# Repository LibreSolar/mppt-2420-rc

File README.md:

# MPPT charge controller for DIN rail mounting

 First prototype tested, but issues should still be expected.

Schematic: [PDF file](https://github.com/LibreSolar/mppt-2420-rc/raw/master/build/mppt-2420-rc_schematic.pdf)

Bill of Materials: [CSV file](build/mppt-2420-rc_bom.csv) or [interactive HTML BOM](https://libre.solar/mppt-2420-rc/build/mppt-2420-rc_ibom.html)

## Concept description

This charge controller is mainly developed to test the following features:

- Very compact and modular housing design for DIN rail mounting
- Thermal performance and maximum heat dissipation via internal heat sinks
- Performance of the internal OpAmp of the STM32G431 MCU for current measurement
- Dump-load control for small wind turbines using the existing PV reverse blocking MOSFET

## Features

- Solar/Wind input terminal
    - Max. 80V (100V MOSFETs used)
    - DC/DC converter inductor current max. 20A
- Battery output terminal
    - 10 V - 32 V (supporting 12 V and 24 V battery systems)
    - Max. current: 20A (limited by inductor current)
- New STM32G431 ARM MCU with advanced digital power conversion features
- Expandable via Olimex Universal Extension Connector (UEXT)
- Only single LED as power indicator. Additional user interface can be included in separate PCB in front panel housing and connected via UEXT
- CAN interface via RJ45 connectors
- Optional external temperature sensor (10k NTC)
- DIN rail mounting using Phoenix Contact BC series housing

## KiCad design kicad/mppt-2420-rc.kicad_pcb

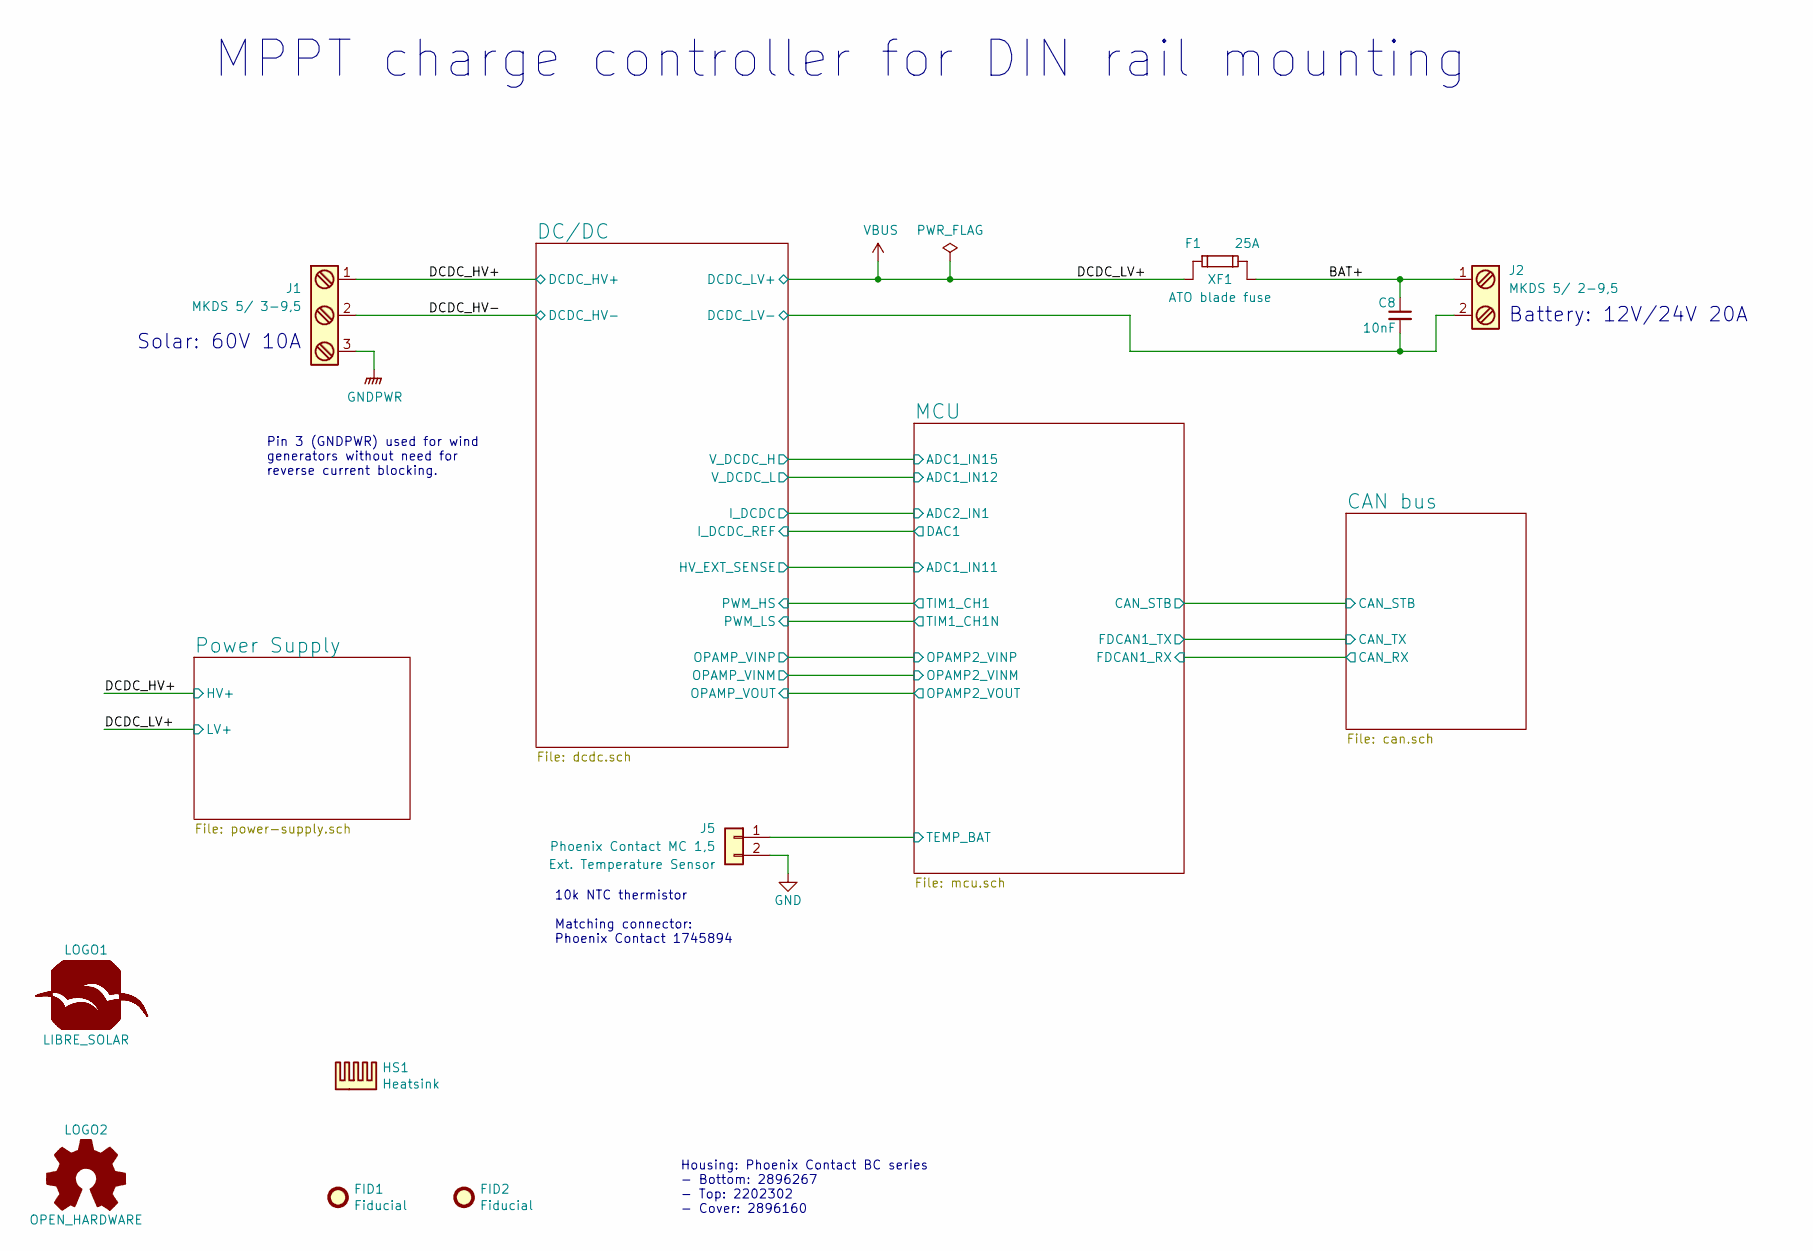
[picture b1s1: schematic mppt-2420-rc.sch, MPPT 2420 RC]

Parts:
C8: 10nF; C_0603_1608; PartNumber GCM188R72A103KA37D
F1: 25A; NULL; PartNumber 0287025.PXCN
FID1, FID2: Fiducial; Fiducial_0.7mm
HS1: Heatsink; Fischer_Elektronik_SK573_37,5; PartNumber SK573-37,5
J1: MKDS 5/ 3-9,5; Phoenix_Contact_MKDS_5-3-9,5; PartNumber 1714984
J2: MKDS 5/ 2-9,5; Phoenix_Contact_MKDS_5-2-9,5; PartNumber 1714971
J5: Phoenix Contact MC 1,5; Phoenix_Contact_MC_1,5_2-G-3,81
LOGO1: LIBRE_SOLAR; LIBRESOLAR_LOGO
LOGO2: OPEN_HARDWARE; OSHW-Logo_5.7x6mm_SilkScreen
XF1: ATO blade fuse; Keystone-Fuse-3557-2

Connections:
/BAT+: C8.1, J2.1, XF1.2
/DCDC_HV+: J1.1; also elsewhere on the board
/DCDC_HV-: J1.2; also elsewhere on the board
/MCU/TEMP_BAT: J5.1; also elsewhere on the board
GND: C8.2, J2.2, J5.2; also elsewhere on the board
GNDPWR: J1.3; also elsewhere on the board
VBUS: XF1.1; also elsewhere on the board

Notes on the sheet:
MPPT charge controller for DIN rail mounting
Solar: 60V 10A
Battery: 12V/24V 20A
Pin 3 (GNDPWR) used for wind generators without need for reverse current blocking.
Housing: Phoenix Contact BC series - Bottom: 2896267 - Top: 2202302 - Cover: 2896160
10k NTC thermistor Matching connector: Phoenix Contact 1745894

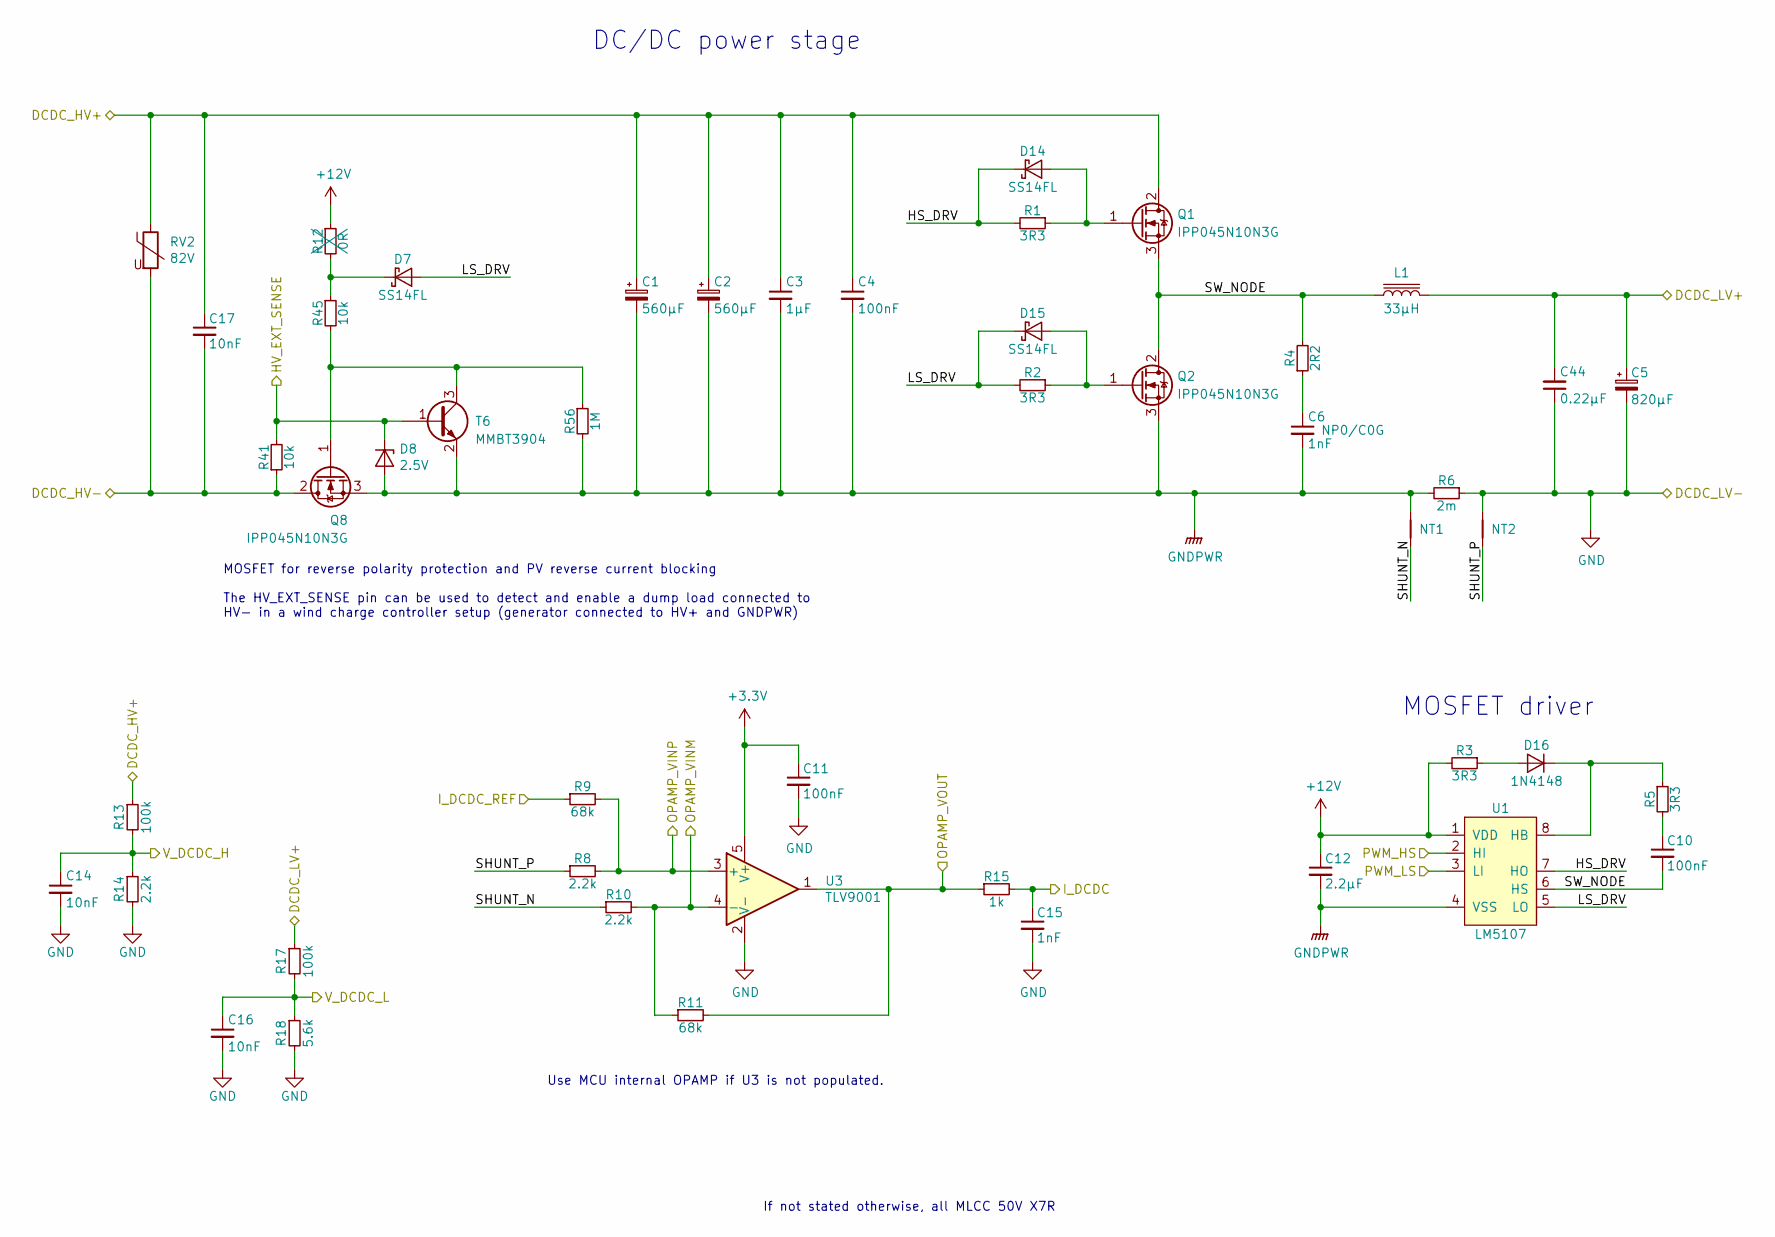
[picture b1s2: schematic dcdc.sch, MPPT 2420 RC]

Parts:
C1, C2: 560µF; CP_Radial_D18.0mm_P7.50mm; PartNumber EKZN101ELL561MM25S
C3: 1µF; C_0805_2012; PartNumber GRJ21BC72A105KE11L
C4: 100nF; C_0805_2012
C5: 820µF; CP_Radial_D10.0mm_P5.00mm; PartNumber EEU-FR1V821L
C6: 1nF; C_0603_1608; PartNumber GRM1885C2A102JA01D
C10, C11: 100nF; C_0603_1608; PartNumber GRM188R71H104KA93D
C12: 2.2µF; C_0603_1608; PartNumber GRM188R61E225KA12D
C14, C16, C17: 10nF; C_0603_1608; PartNumber GCM188R72A103KA37D
C15: 1nF; C_0603_1608
C44: 0.22µF; C_Rect_L7.2mm_W3.5mm_P5.00mm_FKS2_FKP2_MKS2_MKP2; PartNumber 224J63
D7, D14, D15: SS14FL; D_SOD-123; PartNumber SS14FL
D8: 2.5V; D_SOD-123; PartNumber MMSZ5222BT1G
D16: 1N4148; D_SOD-123; PartNumber 1N4148W-7-F
L1: 33µH; L-FERYSTER-DTMSS-27; PartNumber DTMSS-27/0,033/20-H
NT1, NT2: Net-Tie_2; NetTie-2_SMD_Pad0.5mm
Q1, Q2, Q8: IPP045N10N3G; TO-220-3_Vertical; PartNumber IPP045N10N3G
R1, R2, R3, R5: 3R3; R_0805_2012; PartNumber RC0805FR-073R3L
R4: 2R2; R_1206_3216; PartNumber RC1206FR-072R2L
R6: 2m; R_Bourns_CRE2512; PartNumber CRE2512-FZ-R002E-3
R8, R10, R14: 2.2k; R_0603_1608; PartNumber RC0603FR-072K2L
R9, R11: 68k; R_0603_1608; PartNumber RC0603FR-0768KL
R12: 0R; R_0603_1608; PartNumber RC0603FR-070RL
R13, R17: 100k; R_0603_1608; PartNumber RC0603FR-07100KL
R15: 1k; R_0603_1608; PartNumber RC0603FR-071KL
R18: 5.6k; R_0603_1608; PartNumber RC0603FR-075K6L
R41, R45: 10k; R_0603_1608; PartNumber RC0603FR-0710KL
R56: 1M; R_0603_1608; PartNumber RC0603FR-071ML
RV2: 82V; RV_Disc_D12mm_W4.3mm_P7.5mm; PartNumber MOV-10D820K
T6: MMBT3904; SOT-23; PartNumber MMBT3904-7-F
U1: LM5107; SOIC-8_3.9x4.9mm_Pitch1.27mm; PartNumber LM5107MAX/NOPB
U3: TLV9001; SOT-23-5; PartNumber TLV9001IDBVR

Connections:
+3V3: C11.1, U3.5 (V+); also elsewhere on the board
+12V: C12.1, R3.2, R12.1, U1.1 (VDD); also elsewhere on the board
/DC/DC/HS_DRV: D14.1 (K), R1.2, U1.7 (HO)
/DC/DC/LS_DRV: D7.2 (A), D15.1 (K), R2.2, U1.5 (LO)
/DC/DC/PWM_HS: U1.2 (HI); also elsewhere on the board
/DC/DC/PWM_LS: U1.3 (LI); also elsewhere on the board
/DC/DC/SHUNT_N: NT1.2, R10.1
/DC/DC/SHUNT_P: NT2.2, R8.1
/DC/DC/SW_NODE: C10.2, L1.1, Q1.3 (S), Q2.2 (D), R4.2, U1.6 (HS)
/DCDC_HV+: C1.1, C2.1, C3.1, C4.1, C17.1, Q1.2 (D), R13.1, RV2.1; also elsewhere on the board
/DCDC_HV-: C17.2, Q8.2 (D), R41.1, RV2.2; also elsewhere on the board
/MCU/ADC1_IN11: D8.1 (K), R41.2, T6.1 (B); also elsewhere on the board
/MCU/ADC1_IN12: C16.1, R17.2, R18.1; also elsewhere on the board
/MCU/ADC1_IN15: C14.1, R13.2, R14.1; also elsewhere on the board
/MCU/ADC2_IN1: C15.1, R15.2; also elsewhere on the board
/MCU/DAC1: R9.1; also elsewhere on the board
/MCU/OPAMP2_VINM: R10.2, R11.1, U3.4 (-); also elsewhere on the board
/MCU/OPAMP2_VINP: R8.2, R9.2, U3.3 (+); also elsewhere on the board
/MCU/OPAMP2_VOUT: R11.2, R15.1, U3.1; also elsewhere on the board
GND: C5.2, C11.2, C14.2, C15.2, C16.2, C44.1, NT2.1, R6.1, R14.2, R18.2, U3.2 (V-); also elsewhere on the board
GNDPWR: C1.2, C2.2, C3.2, C4.2, C6.2, C12.2, D8.2 (A), NT1.1, Q2.3 (S), Q8.3 (S), R6.2, R56.2, T6.2 (E), U1.4 (VSS); also elsewhere on the board
unnamed: C6.1, R4.1
unnamed: C10.1, R5.2
unnamed: D7.1 (K), R12.2, R45.1
unnamed: D14.2 (A), Q1.1 (G), R1.1
unnamed: D15.2 (A), Q2.1 (G), R2.1
unnamed: D16.1 (K), R5.1, U1.8 (HB)
unnamed: D16.2 (A), R3.1
unnamed: Q8.1 (G), R45.2, R56.1, T6.3 (C)
VBUS: C5.1, C44.2, L1.2, R17.1; also elsewhere on the board

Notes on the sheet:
DC/DC power stage
MOSFET driver
If not stated otherwise, all MLCC 50V X7R
MOSFET for reverse polarity protection and PV reverse current blocking The HV_EXT_SENSE pin can be used to detect and enable a dump load connected to HV- in a wind charge controller setup (generator connected to HV+ and GNDPWR)
Use MCU internal OPAMP if U3 is not populated.

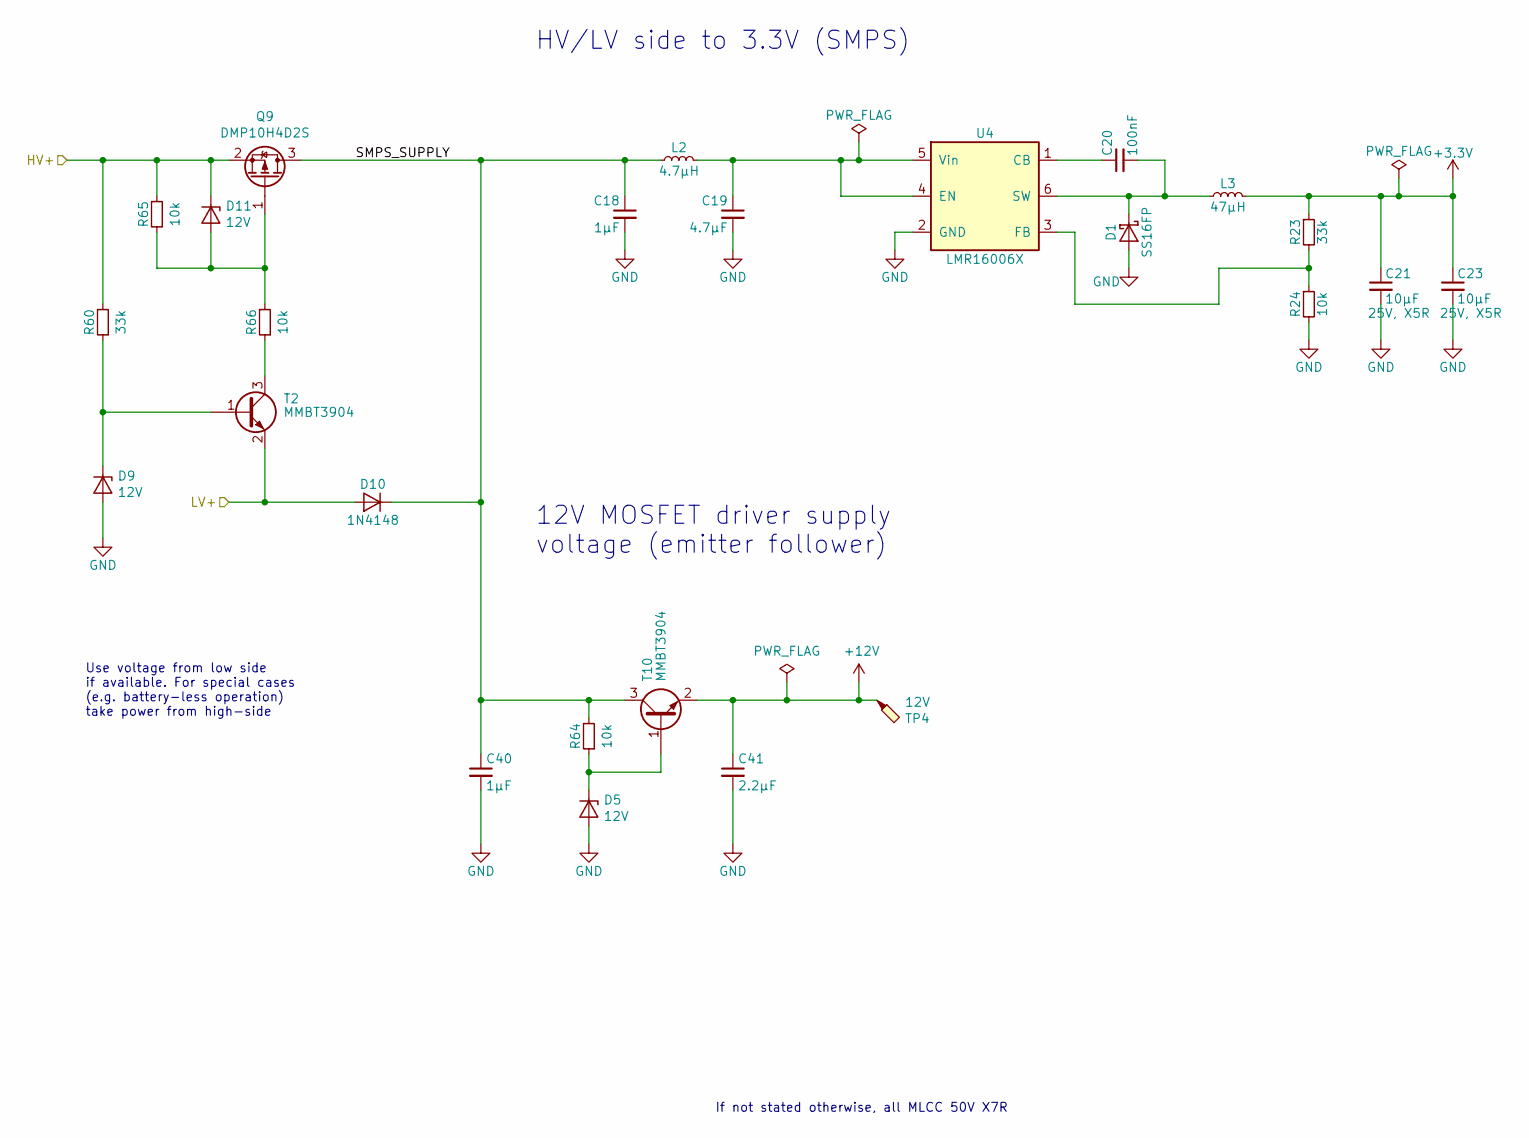
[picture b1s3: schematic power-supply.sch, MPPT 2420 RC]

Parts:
C18, C40: 1µF; C_0805_2012; PartNumber GRJ21BC72A105KE11L
C19: 4.7µF; C_1210_3225; PartNumber GRJ32DC72A475KE11L
C20: 100nF; C_0603_1608; PartNumber GRM188R71H104KA93D
C21, C23: 10µF; C_0805_2012; PartNumber GRM21BR61E106KA73L
C41: 2.2µF; C_0603_1608; PartNumber GRM188R61E225KA12D
D1: SS16FP; D_PowerDI-123; PartNumber SS16FP
D5, D9, D11: 12V; D_SOT-23_ANK; PartNumber SZBZX84C12LT3G
D10: 1N4148; D_SOD-123; PartNumber 1N4148W-7-F
L2: 4.7µH; L_0805_2012Metric; PartNumber LQM21PN4R7NGRD
L3: 47µH; Bourns_SRN6045TA; PartNumber NR6045T470M
Q9: DMP10H4D2S; SOT-23; PartNumber DMP10H4D2S-7
R23, R60: 33k; R_0603_1608; PartNumber RC0603FR-0733KL
R24, R64, R65, R66: 10k; R_0603_1608; PartNumber RC0603FR-0710KL
T2, T10: MMBT3904; SOT-23; PartNumber MMBT3904-7-F
TP4: 12V; TestPoint_Pad_D1.0mm
U4: LMR16006X; SOT-23-6; PartNumber LMR16006XDDCR

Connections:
+3V3: C21.1, C23.1, L3.2, R23.1; also elsewhere on the board
+12V: C41.1, T10.2 (E), TP4.1; also elsewhere on the board
/DCDC_HV+: D11.1 (K), Q9.2 (S), R60.2, R65.2; also elsewhere on the board
/Power Supply/SMPS_SUPPLY: C18.1, C40.1, D10.1 (K), L2.1, Q9.3 (D), R64.2, T10.3 (C)
GND: C18.2, C19.2, C21.2, C23.2, C40.2, C41.2, D1.2 (A), D5.2 (A), D9.2 (A), R24.2, U4.2 (GND); also elsewhere on the board
unnamed: C19.1, L2.2, U4.4 (EN), U4.5 (Vin)
unnamed: C20.1, U4.1 (CB)
unnamed: C20.2, D1.1 (K), L3.1, U4.6 (SW)
unnamed: D5.1 (K), R64.1, T10.1 (B)
unnamed: D9.1 (K), R60.1, T2.1 (B)
unnamed: D11.2 (A), Q9.1 (G), R65.1, R66.2
unnamed: R23.2, R24.1, U4.3 (FB)
unnamed: R66.1, T2.3 (C)
VBUS: D10.2 (A), T2.2 (E); also elsewhere on the board

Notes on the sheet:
HV/LV side to 3.3V (SMPS)
If not stated otherwise, all MLCC 50V X7R
12V MOSFET driver supply voltage (emitter follower)
Use voltage from low side if available. For special cases (e.g. battery-less operation) take power from high-side

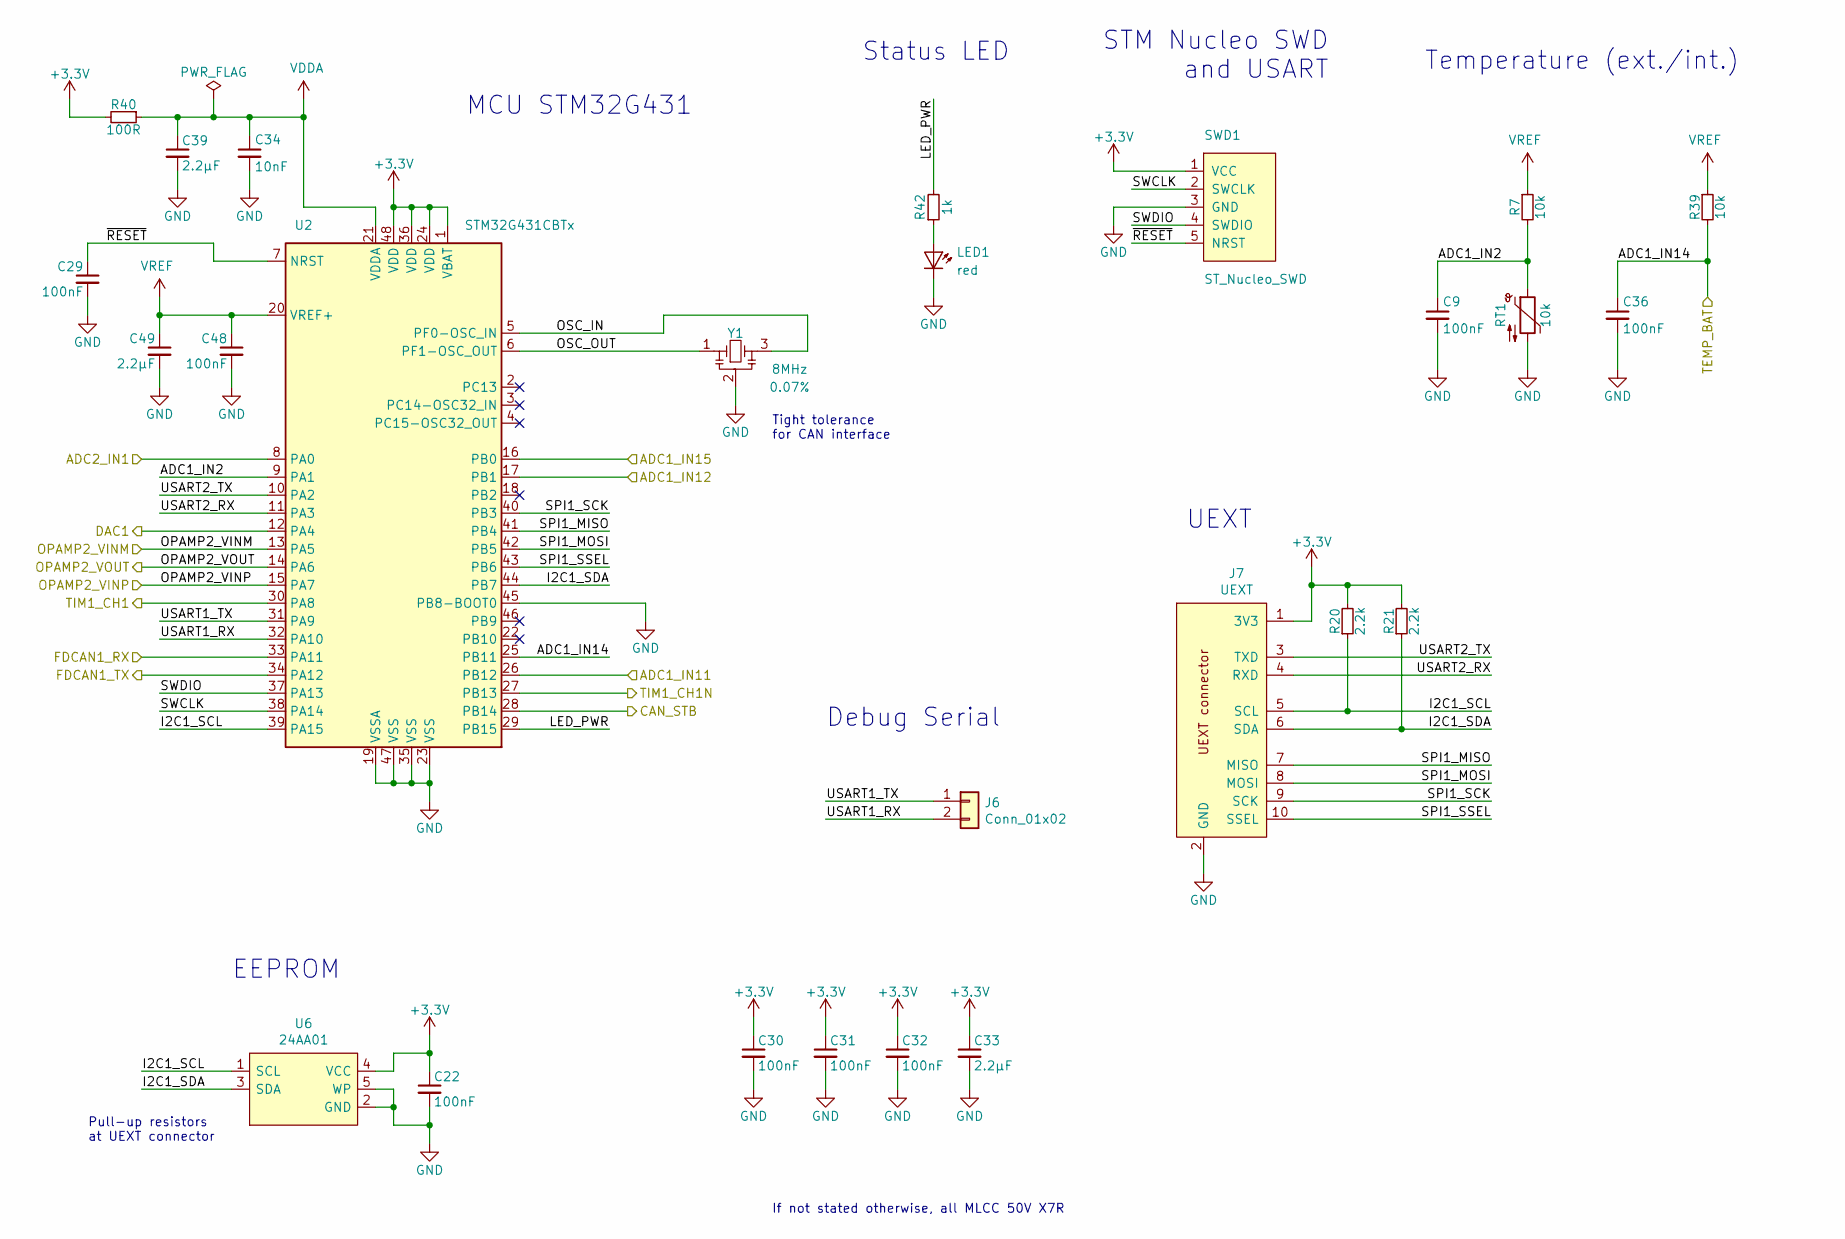
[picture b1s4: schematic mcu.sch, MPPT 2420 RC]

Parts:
C9, C22, C29, C30, C31, C32, C36, C48: 100nF; C_0603_1608; PartNumber GRM188R71H104KA93D
C33, C39, C49: 2.2µF; C_0603_1608; PartNumber GRM188R61E225KA12D
C34: 10nF; C_0603_1608; PartNumber GCM188R72A103KA37D
J6: Conn_01x02; PinHeader_1x02_P2.54mm_Vertical
J7: UEXT; Box_Header_2x05x2.54mm_Straight
LED1: red; LED_D3.0mm; PartNumber LTST-C190KRKT
R7, R39: 10k; R_0603_1608; PartNumber RC0603FR-0710KL
R20, R21: 2.2k; R_0603_1608; PartNumber RC0603FR-072K2L
R40: 100R; R_0603_1608; PartNumber RC0603FR-07100RL
R42: 1k; R_0603_1608; PartNumber RC0603FR-071KL
RT1: 10k; R_0603_1608; PartNumber NTCG163JF103FT1S
SWD1: ST_Nucleo_SWD; PinHeader_1x05_P2.54mm_Vertical; PartNumber Standard 2.54 mm pitch 1x5 pin header
U2: STM32G431CBTx; LQFP-48_7x7mm_P0.5mm; PartNumber STM32G431CBT6
U6: 24AA01; SOT-23-5; PartNumber 24AA32AFT-I/OT
Y1: 8MHz; Resonator_Murata_CSTNE; PartNumber CSTNE8M00GH5C000R0

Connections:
+3V3: C22.1, C30.1, C31.1, C32.1, C33.1, J7.1 (3V3), R20.2, R21.2, R40.2, SWD1.1 (VCC), U2.1 (VBAT), U2.24 (VDD), U2.36 (VDD), U2.48 (VDD), U6.4 (VCC); also elsewhere on the board
/CAN bus/CAN_RX: U2.33 (PA11); also elsewhere on the board
/CAN bus/CAN_STB: U2.28 (PB14); also elsewhere on the board
/CAN bus/CAN_TX: U2.34 (PA12); also elsewhere on the board
/DC/DC/PWM_HS: U2.30 (PA8); also elsewhere on the board
/DC/DC/PWM_LS: U2.27 (PB13); also elsewhere on the board
/MCU/ADC1_IN2: C9.1, R7.2, RT1.1, U2.9 (PA1)
/MCU/ADC1_IN11: U2.26 (PB12); also elsewhere on the board
/MCU/ADC1_IN12: U2.17 (PB1); also elsewhere on the board
/MCU/ADC1_IN15: U2.16 (PB0); also elsewhere on the board
/MCU/ADC2_IN1: U2.8 (PA0); also elsewhere on the board
/MCU/DAC1: U2.12 (PA4); also elsewhere on the board
/MCU/I2C1_SCL: J7.5 (SCL), R20.1, U2.39 (PA15), U6.1 (SCL)
/MCU/I2C1_SDA: J7.6 (SDA), R21.1, U2.44 (PB7), U6.3 (SDA)
/MCU/LED_PWR: R42.2, U2.29 (PB15)
/MCU/OPAMP2_VINM: U2.13 (PA5); also elsewhere on the board
/MCU/OPAMP2_VINP: U2.15 (PA7); also elsewhere on the board
/MCU/OPAMP2_VOUT: U2.14 (PA6); also elsewhere on the board
/MCU/OSC_IN: U2.5 (PF0-OSC_IN), Y1.3
/MCU/OSC_OUT: U2.6 (PF1-OSC_OUT), Y1.1
/MCU/SPI1_MISO: J7.7 (MISO), U2.41 (PB4)
/MCU/SPI1_MOSI: J7.8 (MOSI), U2.42 (PB5)
/MCU/SPI1_SCK: J7.9 (SCK), U2.40 (PB3)
/MCU/SPI1_SSEL: J7.10 (SSEL), U2.43 (PB6)
/MCU/SWCLK: SWD1.2 (SWCLK), U2.38 (PA14)
/MCU/SWDIO: SWD1.4 (SWDIO), U2.37 (PA13)
/MCU/TEMP_BAT: C36.1, R39.2, U2.25 (PB11); also elsewhere on the board
/MCU/USART1_RX: J6.2, U2.32 (PA10)
/MCU/USART1_TX: J6.1, U2.31 (PA9)
/MCU/USART2_RX: J7.4 (RXD), U2.11 (PA3)
/MCU/USART2_TX: J7.3 (TXD), U2.10 (PA2)
/MCU/~RESET: C29.1, SWD1.5 (NRST), U2.7 (NRST)
GND: C9.2, C22.2, C29.2, C30.2, C31.2, C32.2, C33.2, C34.2, C36.2, C39.2, C48.2, C49.2, J7.2 (GND), LED1.1 (K), RT1.2, SWD1.3 (GND), U2.19 (VSSA), U2.23 (VSS), U2.35 (VSS), U2.45 (PB8-BOOT0), U2.47 (VSS), U6.2 (GND), U6.5 (WP), Y1.2; also elsewhere on the board
unnamed: LED1.2 (A), R42.1
VDDA: C34.1, C39.1, R40.1, U2.21 (VDDA)
VREF: C48.1, C49.1, R7.1, R39.1, U2.20 (VREF+)

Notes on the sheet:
Status LED
MCU STM32G431
STM Nucleo SWD and USART
Tight tolerance for CAN interface
EEPROM
If not stated otherwise, all MLCC 50V X7R
Temperature (ext./int.)
UEXT
Pull-up resistors at UEXT connector
Debug Serial

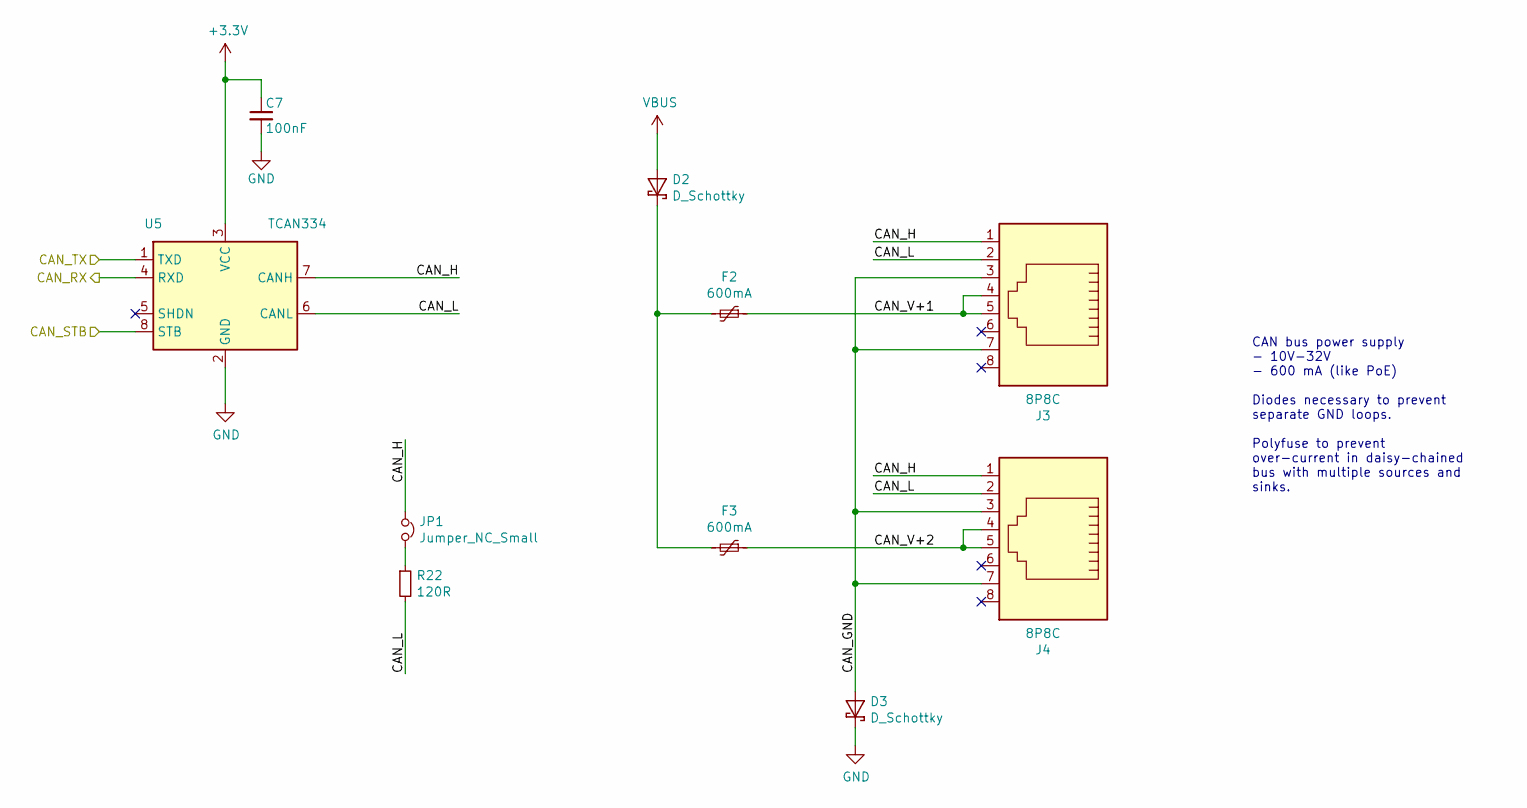
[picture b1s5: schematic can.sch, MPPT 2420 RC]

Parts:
C7: 100nF; C_0603_1608; PartNumber GRM188R71H104KA93D
D2, D3: D_Schottky; D_SOD-123; PartNumber NRVTS260ESFT1G
F2, F3: 600mA; Fuse_1206_3216Metric
J3, J4: 8P8C; RJ45_8P8C; PartNumber 54602-908LF
JP1: Jumper_NC_Small; PinHeader_1x02_P2.54mm_Vertical
R22: 120R; R_1206_3216
U5: TCAN334; SOIC-8_3.9x4.9mm_Pitch1.27mm; PartNumber TCAN334

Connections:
+3V3: C7.1, U5.3 (VCC); also elsewhere on the board
/CAN bus/CAN_GND: D3.2 (A), J3.3, J3.7, J4.3, J4.7
/CAN bus/CAN_H: J3.1, J4.1, JP1.1, U5.7 (CANH)
/CAN bus/CAN_L: J3.2, J4.2, R22.2, U5.6 (CANL)
/CAN bus/CAN_RX: U5.4 (RXD); also elsewhere on the board
/CAN bus/CAN_STB: U5.8 (STB); also elsewhere on the board
/CAN bus/CAN_TX: U5.1 (TXD); also elsewhere on the board
/CAN bus/CAN_V+1: F2.1, J3.4, J3.5
/CAN bus/CAN_V+2: F3.1, J4.4, J4.5
GND: C7.2, D3.1 (K), U5.2 (GND); also elsewhere on the board
unnamed: D2.1 (K), F2.2, F3.2
unnamed: JP1.2, R22.1
VBUS: D2.2 (A); also elsewhere on the board

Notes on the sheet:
CAN bus power supply - 10V-32V - 600 mA (like PoE) Diodes necessary to prevent separate GND loops. Polyfuse to prevent over-current in daisy-chained bus with multiple sources and sinks.

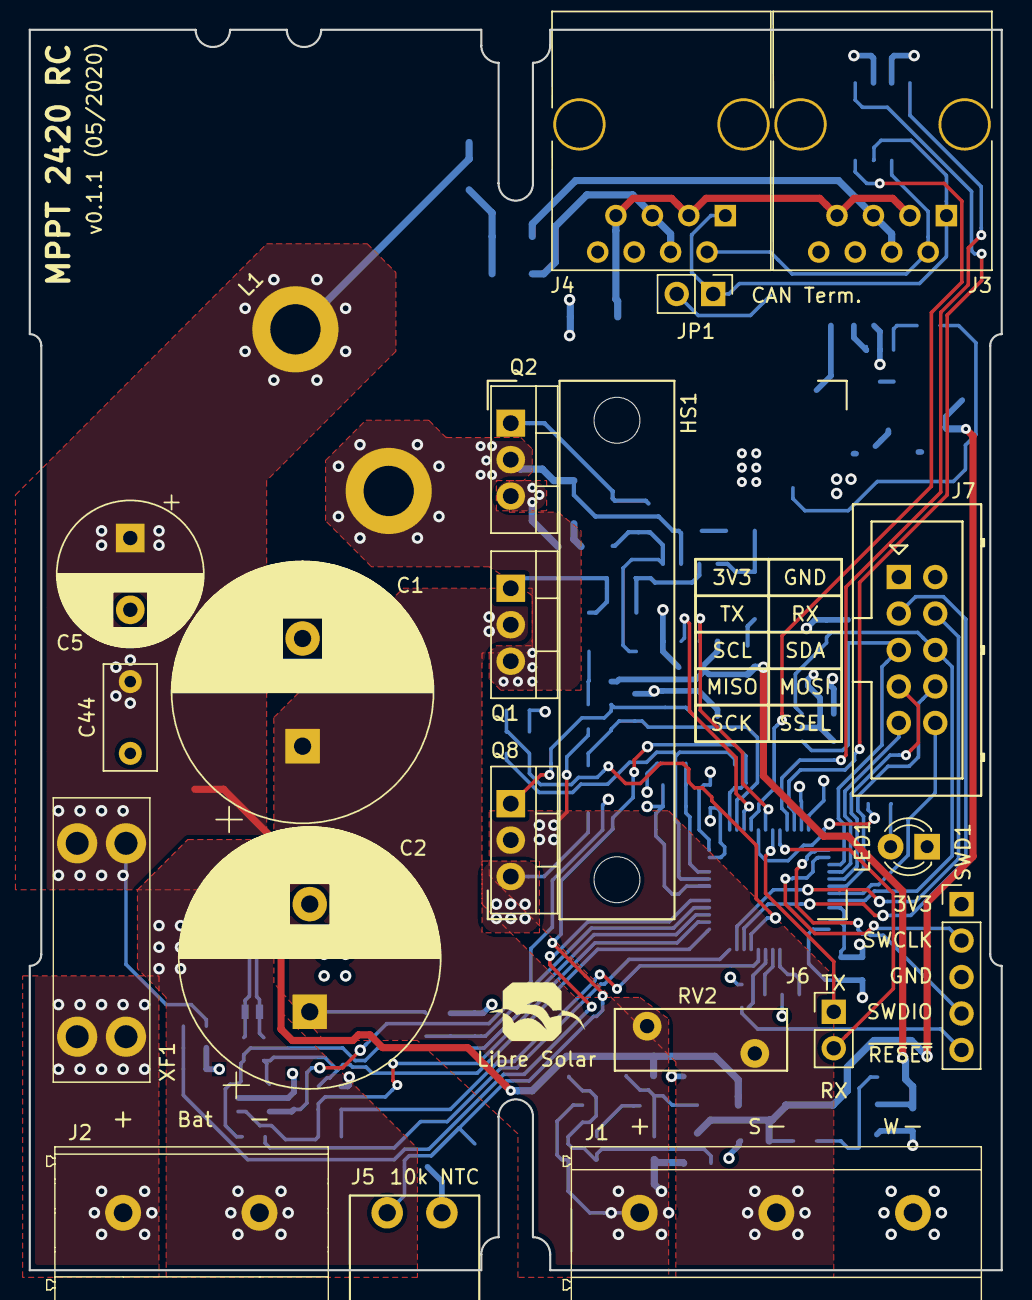
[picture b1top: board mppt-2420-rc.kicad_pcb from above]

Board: 4 copper layers, 67.7 x 86.4 mm, 120 parts (0 on the bottom side), 71 nets.

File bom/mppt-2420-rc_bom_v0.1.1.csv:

Component,Description,Part,References,Value,Footprint,Quantity Per PCB,Datasheet,PartNumber,Manufacturer,Remarks,Alternative,Supplier,DNP
1,Unpolarized capacitor,C,C44,0.22µF,C_Rect_L7.2mm_W3.5mm_P5.00mm_FKS2_FKP2_MKS2_MKP2,1,,224J63,,,,,
2,Unpolarized capacitor,C,C7 C9 C10 C11 C20 C22 C29 C30 C31 C32 C36 C48,100nF,C_0603_1608,12,,GRM188R71H104KA93D,Murata,,,,
3,Unpolarized capacitor,C,C4,100nF,C_0805_2012,1,,,Murata,"100V, X7S",,,
4,Unpolarized capacitor,C,C8 C14 C16 C17 C34,10nF,C_0603_1608,5,,GCM188R72A103KA37D,Murata,"100V, X7R",,,
5,Unpolarized capacitor,C,C21 C23,10µF,C_0805_2012,2,,GRM21BR61E106KA73L,Murata,"25V, X5R",,,
6,Unpolarized capacitor,C,C15,1nF,C_0603_1608,1,,,,"50V, NP0/C0G",,,
7,Unpolarized capacitor,C,C6,1nF,C_0603_1608,1,,GRM1885C2A102JA01D,Murata,NP0/C0G,,,
8,Unpolarized capacitor,C,C3 C18 C40,1µF,C_0805_2012,3,,GRJ21BC72A105KE11L,Murata,"100V, X7S",,,
9,Unpolarized capacitor,C,C12 C33 C39 C41 C49,2.2µF,C_0603_1608,5,,GRM188R61E225KA12D,Murata,"25V, X5R",,,
10,Unpolarized capacitor,C,C19,4.7µF,C_1210_3225,1,,GRJ32DC72A475KE11L,Murata,"100V, X7S",,,
11,"Polarized capacitor, small symbol",CP_Small,C1 C2,560µF,CP_Radial_D18.0mm_P7.50mm,2,,EKZN101ELL561MM25S,United Chemi-Con,"100V, 2.27A, 18x25",,,
12,"Polarized capacitor, small symbol",CP_Small,C5,820µF,CP_Radial_D10.0mm_P5.00mm,1,,EEU-FR1V821L,Panasonic,"35V, 2.47A",,,
13,Diode zener,D_Zener,D5 D9 D11,12V,D_SOT-23_ANK,3,,SZBZX84C12LT3G,ON Semiconductor,Alternative: Diodes Inc. BZX84C12-7-F,,,
14,Diode,D,D10 D16,1N4148,D_SOD-123,2,,1N4148W-7-F,Diodes Inc.,,,,
15,Diode zener,D_Zener,D8,2.5V,D_SOD-123,1,,MMSZ5222BT1G,ON Semiconductor,,,,
16,Diode Schottky,D_Schottky,D2 D3,D_Schottky,D_SOD-123,2,,NRVTS260ESFT1G,ON Semiconductor,"Alternative: Nexperia PMEG6020ER,115",,,
17,Diode Schottky,D_Schottky,D7 D14 D15,SS14FL,D_SOD-123,3,,SS14FL,ON Semiconductor,,Nexperia PMEG4010EGWX,,
18,Diode Schottky,D_Schottky,D1,SS16FP,D_PowerDI-123,1,,SS16FP,Diodes Inc.,,DFLS160-7,,
19,Fuse plug-in,Fuse_PlugIn,F1,25A,NULL,1,,0287025.PXCN,Littelfuse,,,,
20,"Resettable fuse, polymeric positive temperature coefficient, small symbol",Polyfuse_Small,F2 F3,600mA,Fuse_1206_3216Metric,2,~,,,,,,
21,Heatsink,Heatsink,HS1,Heatsink,"Fischer_Elektronik_SK573_37,5",1,~,"SK573-37,5",Fischer Elektronik,3x MOSFET clips THFU 2 and thermal interface material needed,,,
22,"RJ connector, 8P8C (8 positions 8 connected), RJ31/RJ32/RJ33/RJ34/RJ35/RJ41/RJ45/RJ49/RJ61",8P8C,J3 J4,8P8C,RJ45_8P8C,2,,54602-908LF,Amphenol FCI,,,,
23,"Generic connector, single row, 01x02, script generated (kicad-library-utils/schlib/autogen/connector/)",Conn_01x02,J6,Conn_01x02,PinHeader_1x02_P2.54mm_Vertical,1,~,,,,,,
24,,Screw_Terminal_1x02,J2,"MKDS 5/ 2-9,5","Phoenix_Contact_MKDS_5-2-9,5",1,,1714971,Phoenix Contact,,,,
25,,Screw_Terminal_1x03_Large,J1,"MKDS 5/ 3-9,5","Phoenix_Contact_MKDS_5-3-9,5",1,,1714984,Phoenix Contact,,,,
26,"Generic connector, single row, 01x02, script generated (kicad-library-utils/schlib/autogen/connector/)",Conn_01x02,J5,"Phoenix Contact MC 1,5","Phoenix_Contact_MC_1,5_2-G-3,81",1,~,,,Ext. Temperature Sensor,,,
27,Olimex UEXT connector (2x5 box header),UEXT,J7,UEXT,Box_Header_2x05x2.54mm_Straight,1,,,,,,,
28,"Jumper, normally closed, small symbol",Jumper_NC_Small,JP1,Jumper_NC_Small,PinHeader_1x02_P2.54mm_Vertical,1,~,,,,,,
29,Inductor with iron core,L_Core_Iron,L1,33µH,L-FERYSTER-DTMSS-27,1,,"DTMSS-27/0,033/20-H",Feryster,,,Feryster,
30,"Inductor, small symbol",L_Small,L2,4.7µH,L_0805_2012Metric,1,,LQM21PN4R7NGRD,Murata,,,,
31,"Inductor, small symbol",L_Small,L3,47µH,Bourns_SRN6045TA,1,,NR6045T470M,Tayo Yuden,,Bourns SRR6045TA-470Y,,
32,,D_LED,LED1,red,LED_D3.0mm,1,,LTST-C190KRKT,Lite-On,red,,,
33,"Net tie, 2 pins",Net-Tie_2,NT1 NT2,Net-Tie_2,NetTie-2_SMD_Pad0.5mm,2,~,,,,,,
34,"P-MOSFET transistor, gate/source/drain",Q_PMOS_GSD,Q9,DMP10H4D2S,SOT-23,1,~,DMP10H4D2S-7,Diodes Inc.,,,,
35,"N-MOSFET transistor, gate/drain/source",Q_NMOS_GDS,Q1 Q2 Q8,IPP045N10N3G,TO-220-3_Vertical,3,,IPP045N10N3G,Infineon,,,,
36,Resistor,R,R12,0R,R_0603_1608,1,,RC0603FR-070RL,Yageo,,,,X
37,Resistor,R,R40,100R,R_0603_1608,1,,RC0603FR-07100RL,Yageo,,,,
38,Resistor,R,R13 R17,100k,R_0603_1608,2,,RC0603FR-07100KL,Yageo,,,,
39,Resistor,R,R7 R24 R39 R41 R45 R64 R65 R66,10k,R_0603_1608,8,,RC0603FR-0710KL,Yageo,,,,
40,Resistor,R,R22,120R,R_1206_3216,1,,,,,,,
41,Resistor,R,R56,1M,R_0603_1608,1,,RC0603FR-071ML,Yageo,,,,
42,Resistor,R,R15 R42,1k,R_0603_1608,2,,RC0603FR-071KL,Yageo,,,,
43,Resistor,R,R8 R10 R14 R20 R21,2.2k,R_0603_1608,5,,RC0603FR-072K2L,Yageo,,,,
44,Resistor,R,R4,2R2,R_1206_3216,1,,RC1206FR-072R2L,Yageo,,,,
45,Resistor,R,R6,2m,R_Bourns_CRE2512,1,,CRE2512-FZ-R002E-3,Bourns,,,,
46,Resistor,R,R23 R60,33k,R_0603_1608,2,,RC0603FR-0733KL,Yageo,,,,
47,Resistor,R,R1 R2 R3 R5,3R3,R_0805_2012,4,,RC0805FR-073R3L,Yageo,,,,
48,Resistor,R,R18,5.6k,R_0603_1608,1,,RC0603FR-075K6L,Yageo,,,,
49,Resistor,R,R9 R11,68k,R_0603_1608,2,,RC0603FR-0768KL,Yageo,,,,
50,"Temperature dependent resistor, negative temperature coefficient",Thermistor_NTC,RT1,10k,R_0603_1608,1,,NTCG163JF103FT1S,TDK,,,,
51,Voltage dependent resistor,Varistor,RV2,82V,RV_Disc_D12mm_W4.3mm_P7.5mm,1,,MOV-10D820K,Bourns,,,,
52,,ST_Nucleo_SWD_5p,SWD1,ST_Nucleo_SWD,PinHeader_1x05_P2.54mm_Vertical,1,,Standard 2.54 mm pitch 1x5 pin header,Any,,,,
53,"0.8A Ic, 45V Vce, NPN Transistor, SOT-23",BC817,T2 T6 T10,MMBT3904,SOT-23,3,http://www.fairchildsemi.com/ds/BC/BC817.pdf,MMBT3904-7-F,Diodes Inc.,,,,
54,Microchip 24AA01 1K I2C EEPROM,24AA01,U6,24AA01,SOT-23-5,1,,24AA32AFT-I/OT,Microchip,,,,
55,,LM5107,U1,LM5107,SOIC-8_3.9x4.9mm_Pitch1.27mm,1,,LM5107MAX/NOPB,Texas Instruments,,,,
56,"SIMPLE SWITCHER® 4V to 60V, 600mA Step-Down Regulator with Low Iq",LMR16006,U4,LMR16006X,SOT-23-6,1,,LMR16006XDDCR,Texas Instruments,,,,
57,"ARM Cortex-M4 MCU, 128KB flash, 22KB RAM, 170MHz, 1.71-3.6V, 66 GPIO, LQFP-48",STM32G431CBTx,U2,STM32G431CBTx,LQFP-48_7x7mm_P0.5mm,1,https://www.st.com/resource/en/datasheet/stm32g431cb.pdf,STM32G431CBT6,ST Microelectronics,,,,
58,"High-Speed CAN Transceiver, 1Mbps, 3.3V supply, low power standby mode, shutdown mode, SOT-23-8/SOIC-8",TCAN334,U5,TCAN334,SOIC-8_3.9x4.9mm_Pitch1.27mm,1,http://www.ti.com/lit/ds/symlink/tcan337.pdf,TCAN334,Texas Instruments,,,,
59,SOT-23-5,OpAmp_Single_Generic,U3,TLV9001,SOT-23-5,1,,TLV9001IDBVR,Texas Instruments,"Alternative: TLV6001, MCP6001",,,
60,Fuse Holder,Fuse_Holder,XF1,ATO blade fuse,Keystone-Fuse-3557-2,1,,,,,,,
61,Two pin crystal,Resonator,Y1,8MHz,Resonator_Murata_CSTNE,1,,CSTNE8M00GH5C000R0,Murata,0.07%,,,

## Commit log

2020-05-15 Initial version ordered (v0.1)
2020-05-31 Fix errors after first prototype build-up
    - Collision of capacitors with MOSFET clamps
    - BOOT0 pin tied to GND
    - Assignment of a few previously unasigned passives
    - Add optional debug serial connector
2020-06-14 Fix some references and part numbers
    See issues #3, #5, #7, #8 and #9.
2020-06-17 Clean up BOM and add build folder for generated files
